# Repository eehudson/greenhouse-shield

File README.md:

# greenhouse-shield
Making a shield that measures temperature, humidity, light, and air quality for an Arduino Uno

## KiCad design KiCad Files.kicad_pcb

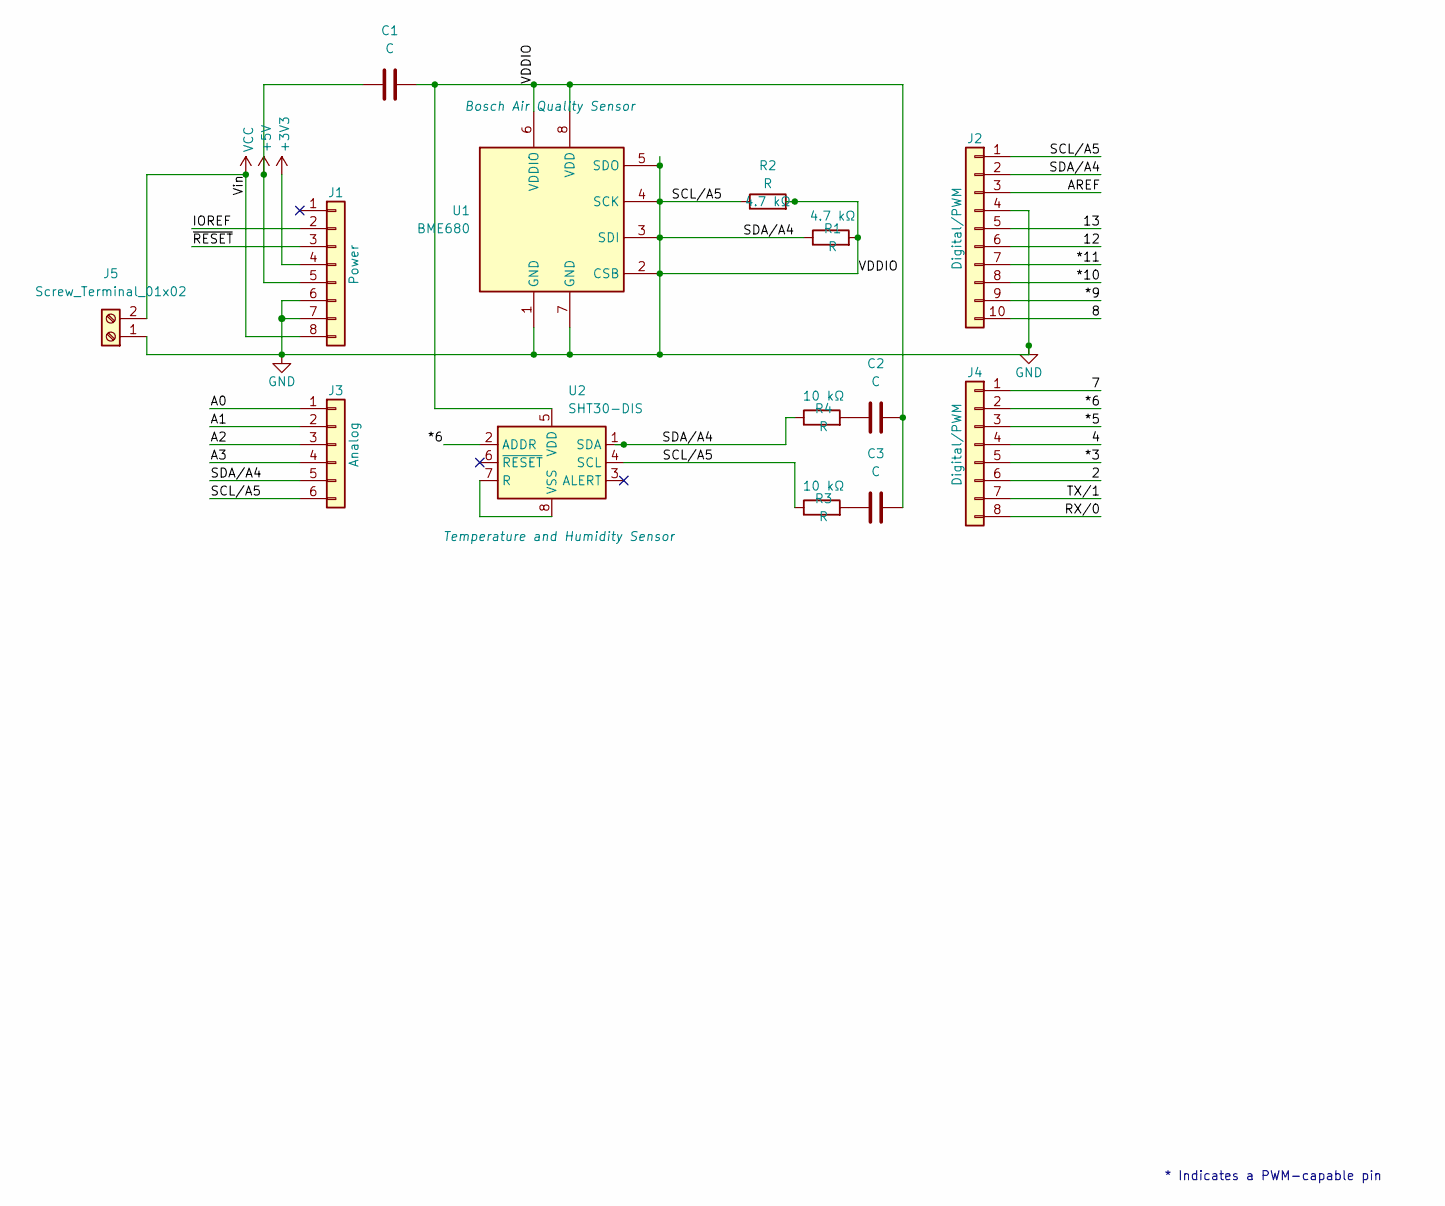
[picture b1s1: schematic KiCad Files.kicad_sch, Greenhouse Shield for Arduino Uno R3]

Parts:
C1, C2, C3: C; C_Axial_L3.8mm_D2.6mm_P7.50mm_Horizontal
J1: Power; PinSocket_1x08_P2.54mm_Vertical
J2: Digital/PWM; PinSocket_1x10_P2.54mm_Vertical
J3: Analog; PinSocket_1x06_P2.54mm_Vertical
J4: Digital/PWM; PinSocket_1x08_P2.54mm_Vertical
J5: Screw_Terminal_01x02; TerminalBlock_Xinya_XY308-2.54-2P_1x02_P2.54mm_Horizontal
R1, R2, R3, R4: R; R_Axial_DIN0204_L3.6mm_D1.6mm_P1.90mm_Vertical
U1: BME680; Bosch_LGA-8_3x3mm_P0.8mm_ClockwisePinNumbering
U2: SHT30-DIS; Sensirion_DFN-8-1EP_2.5x2.5mm_P0.5mm_EP1.1x1.7mm

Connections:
+3V3: J1.4
+5V: C1.2, J1.5
/2: J4.6
/4: J4.4
/7: J4.1
/8: J2.10
/12: J2.6
/13: J2.5
/*3: J4.5
/*5: J4.3
/*6: J4.2, U2.2 (ADDR)
/*9: J2.9
/*10: J2.8
/*11: J2.7
/A0: J3.1
/A1: J3.2
/A2: J3.3
/A3: J3.4
/AREF: J2.3
/IOREF: J1.2
/RX/0: J4.8
/TX/1: J4.7
/~RESET: J1.3
GND: C1.1, C2.1, C3.1, J1.6, J1.7, J2.1, J2.2, J2.4, J3.5, J3.6, J5.1, R1.1, R1.2, R2.1, R2.2, R3.1, R4.1, U1.1 (GND), U1.2 (CSB), U1.3 (SDI), U1.4 (SCK), U1.5 (SDO), U1.6 (VDDIO), U1.7 (GND), U1.8 (VDD), U2.1 (SDA), U2.4 (SCL), U2.5 (VDD)
unnamed: C2.2, R4.2
unnamed: C3.2, R3.2
unnamed: U2.7 (R), U2.8 (VSS), U2.9 (VSS)
VCC: J1.8, J5.2

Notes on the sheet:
* Indicates a PWM-capable pin

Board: 2 copper layers, 18 parts (0 on the bottom side), 7 nets, no tracks yet.

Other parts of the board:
MH1, MH2, MH3, MH4: MountingHole_3.2mm

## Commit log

2025-01-10 Added Base Template and Title to Schematic
2025-01-10 Added Connections to BME680
    Configured based on datasheet for 12C communication protocol.
2025-01-10 Added SHT30 Part and Connections
    Added labels.
2025-01-10 FinalSchematicPDF Added
2025-01-10 Rename KiCad Files.pdf to FinalSchematicPDF.pdf
    changed the name of the file
